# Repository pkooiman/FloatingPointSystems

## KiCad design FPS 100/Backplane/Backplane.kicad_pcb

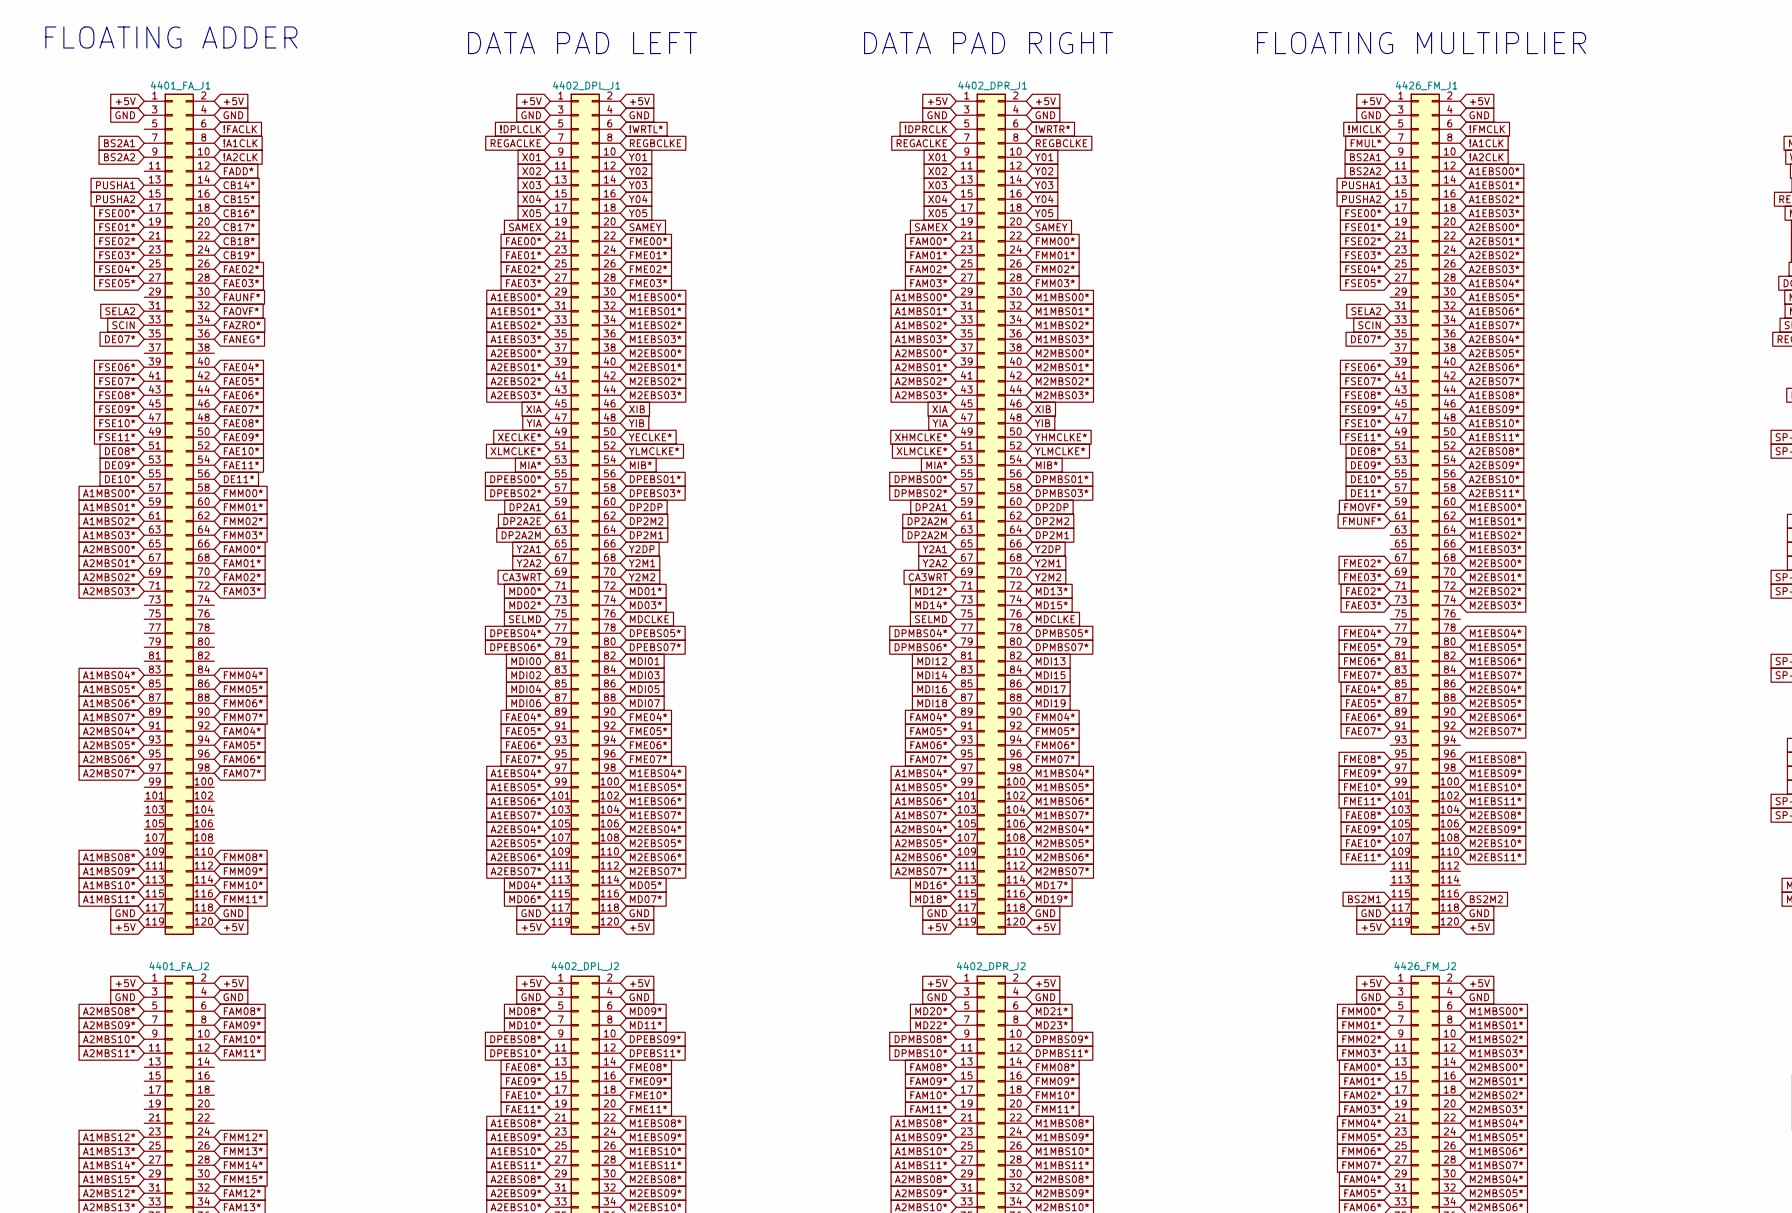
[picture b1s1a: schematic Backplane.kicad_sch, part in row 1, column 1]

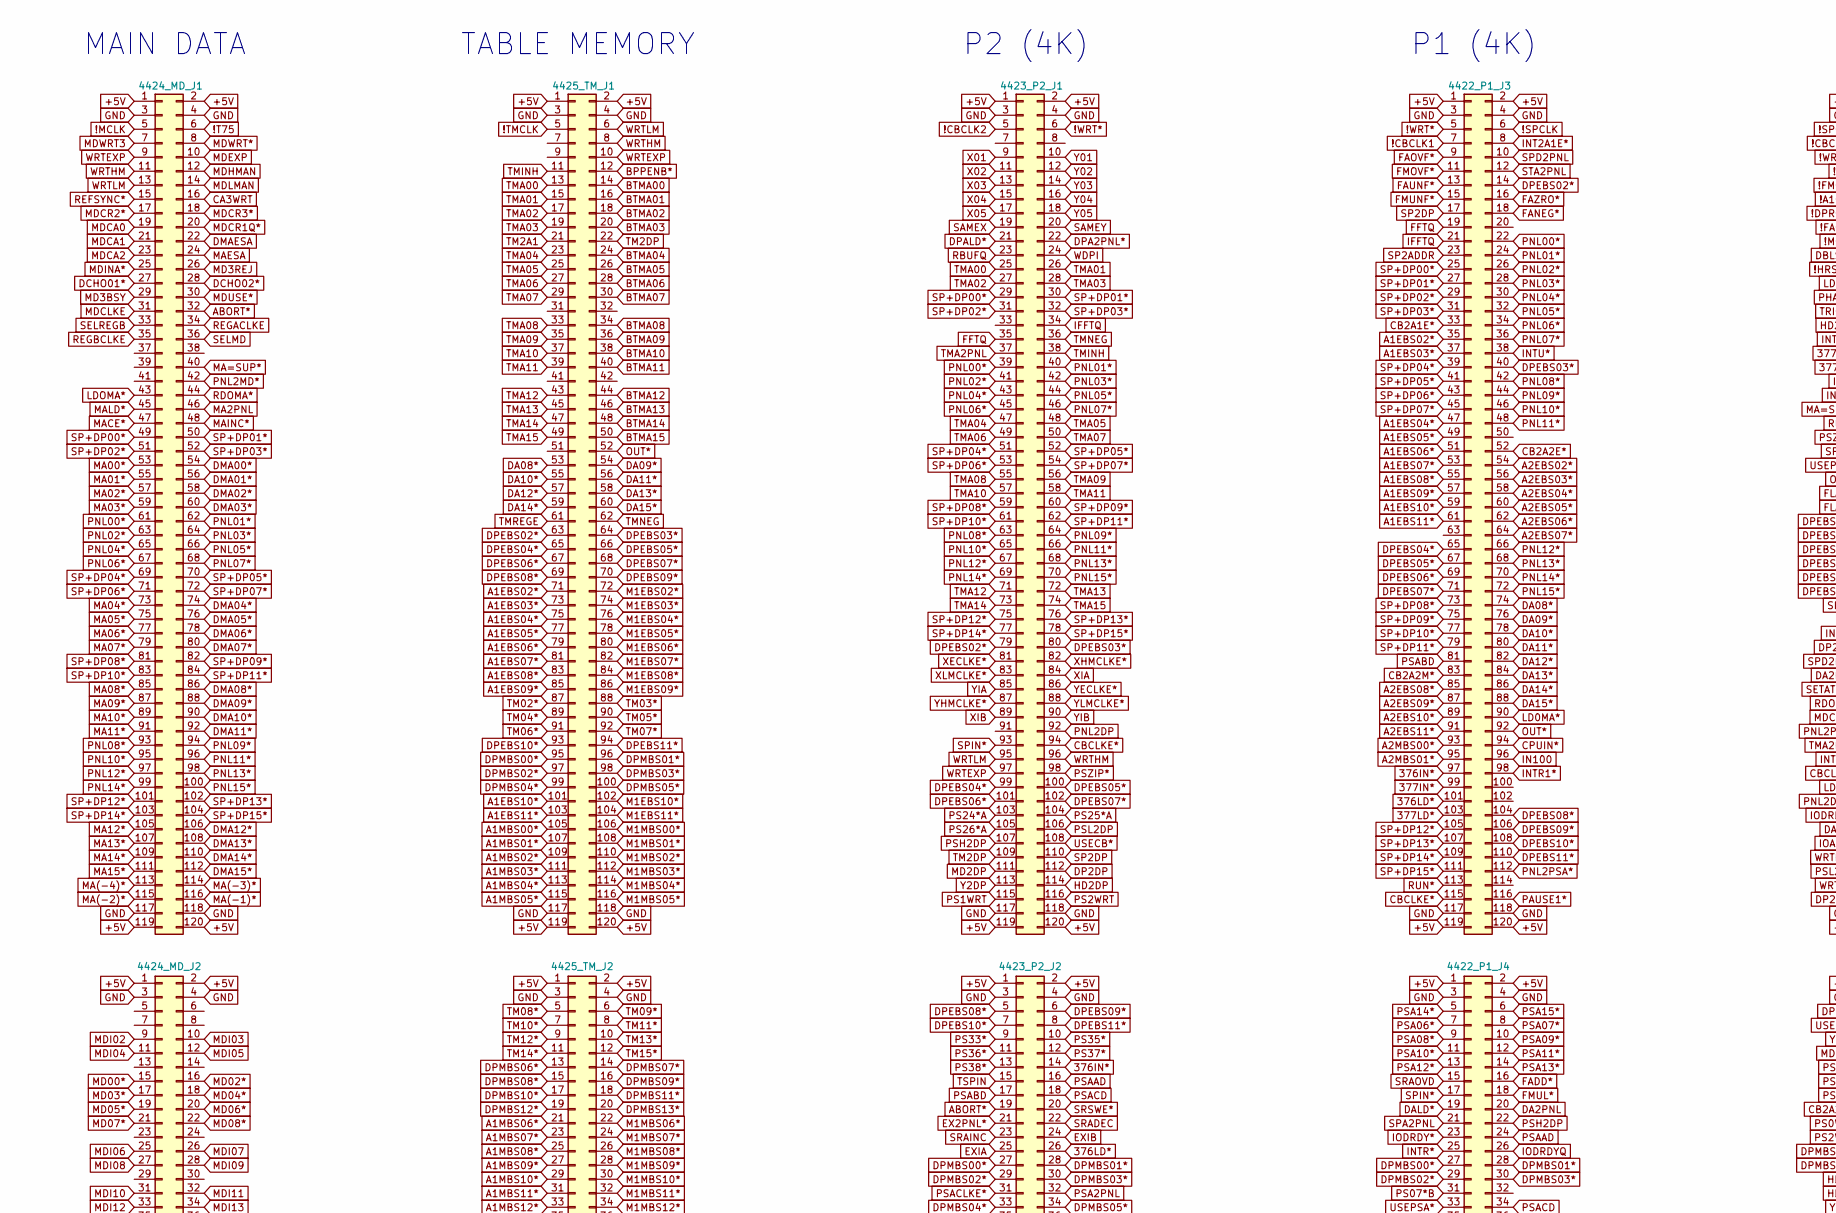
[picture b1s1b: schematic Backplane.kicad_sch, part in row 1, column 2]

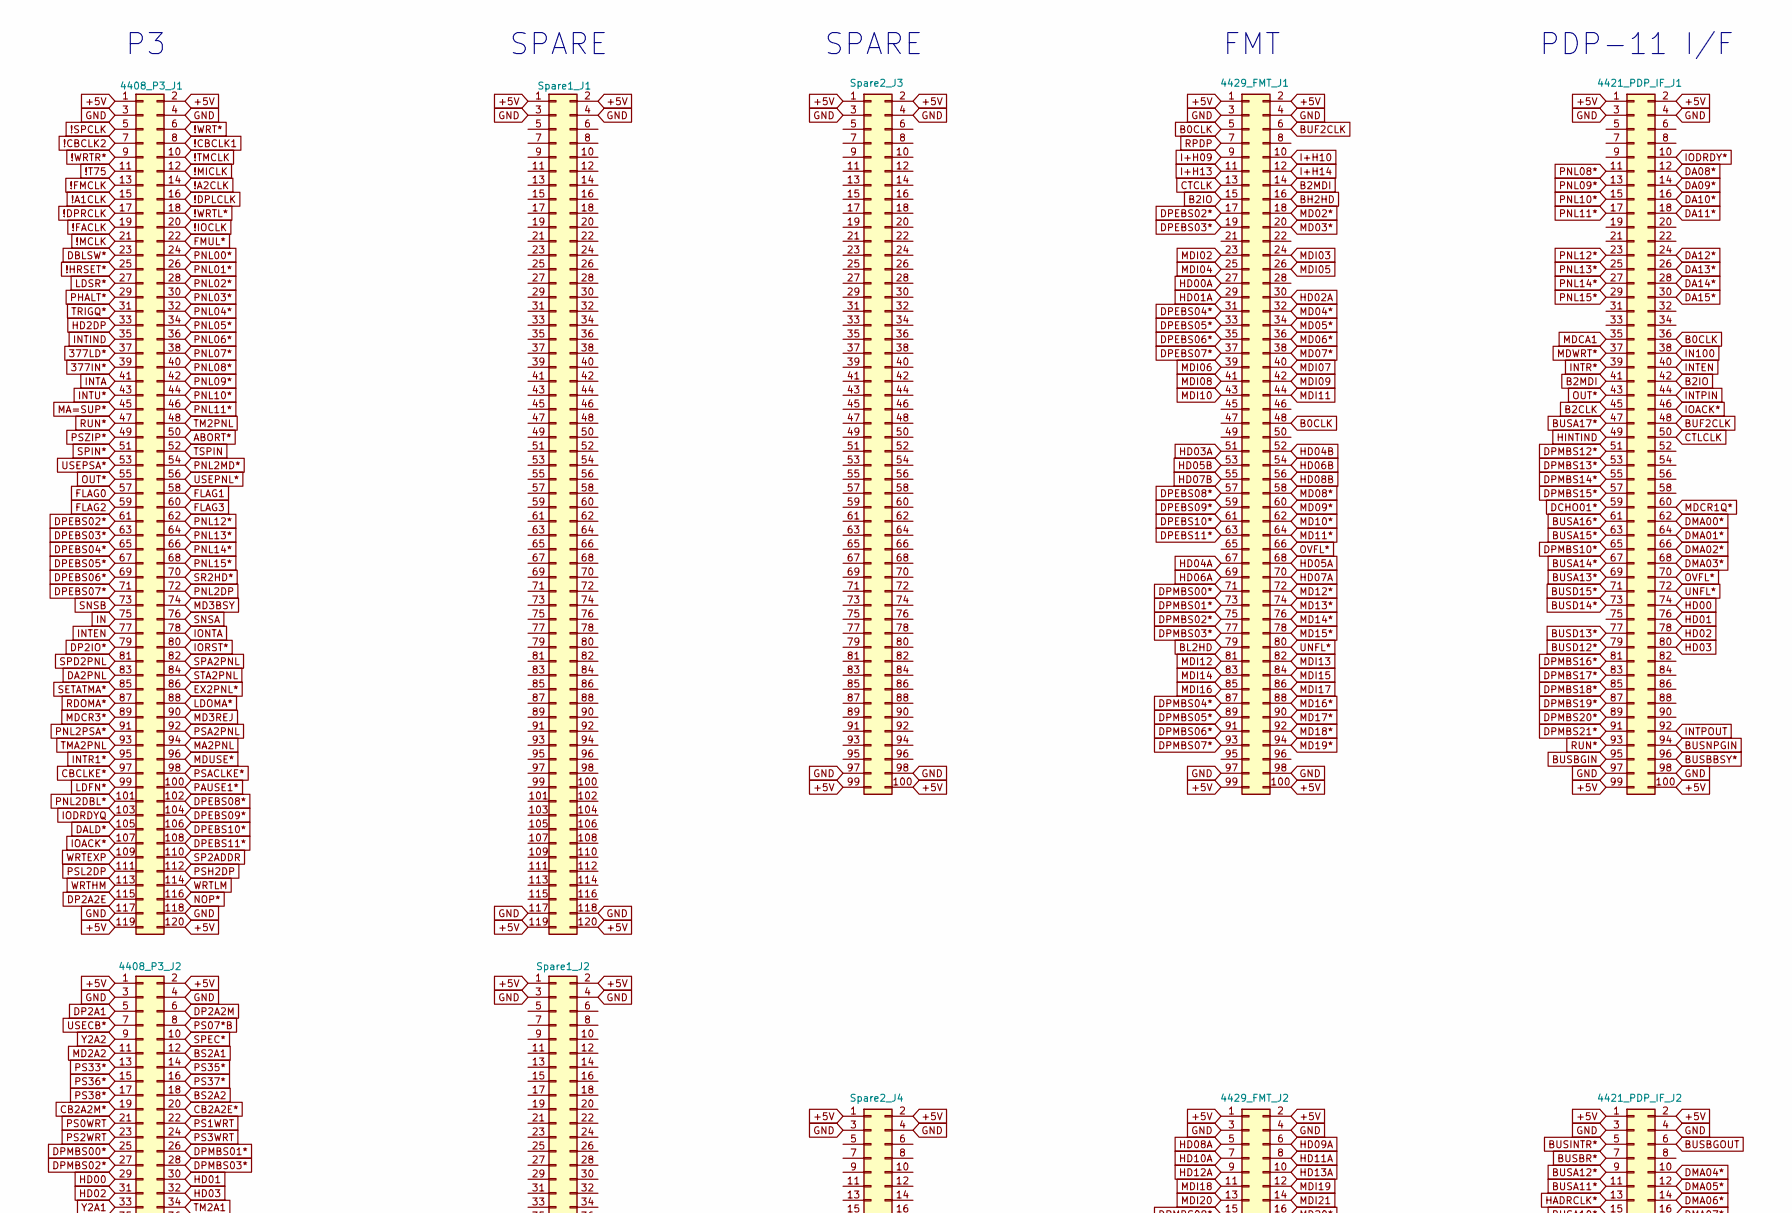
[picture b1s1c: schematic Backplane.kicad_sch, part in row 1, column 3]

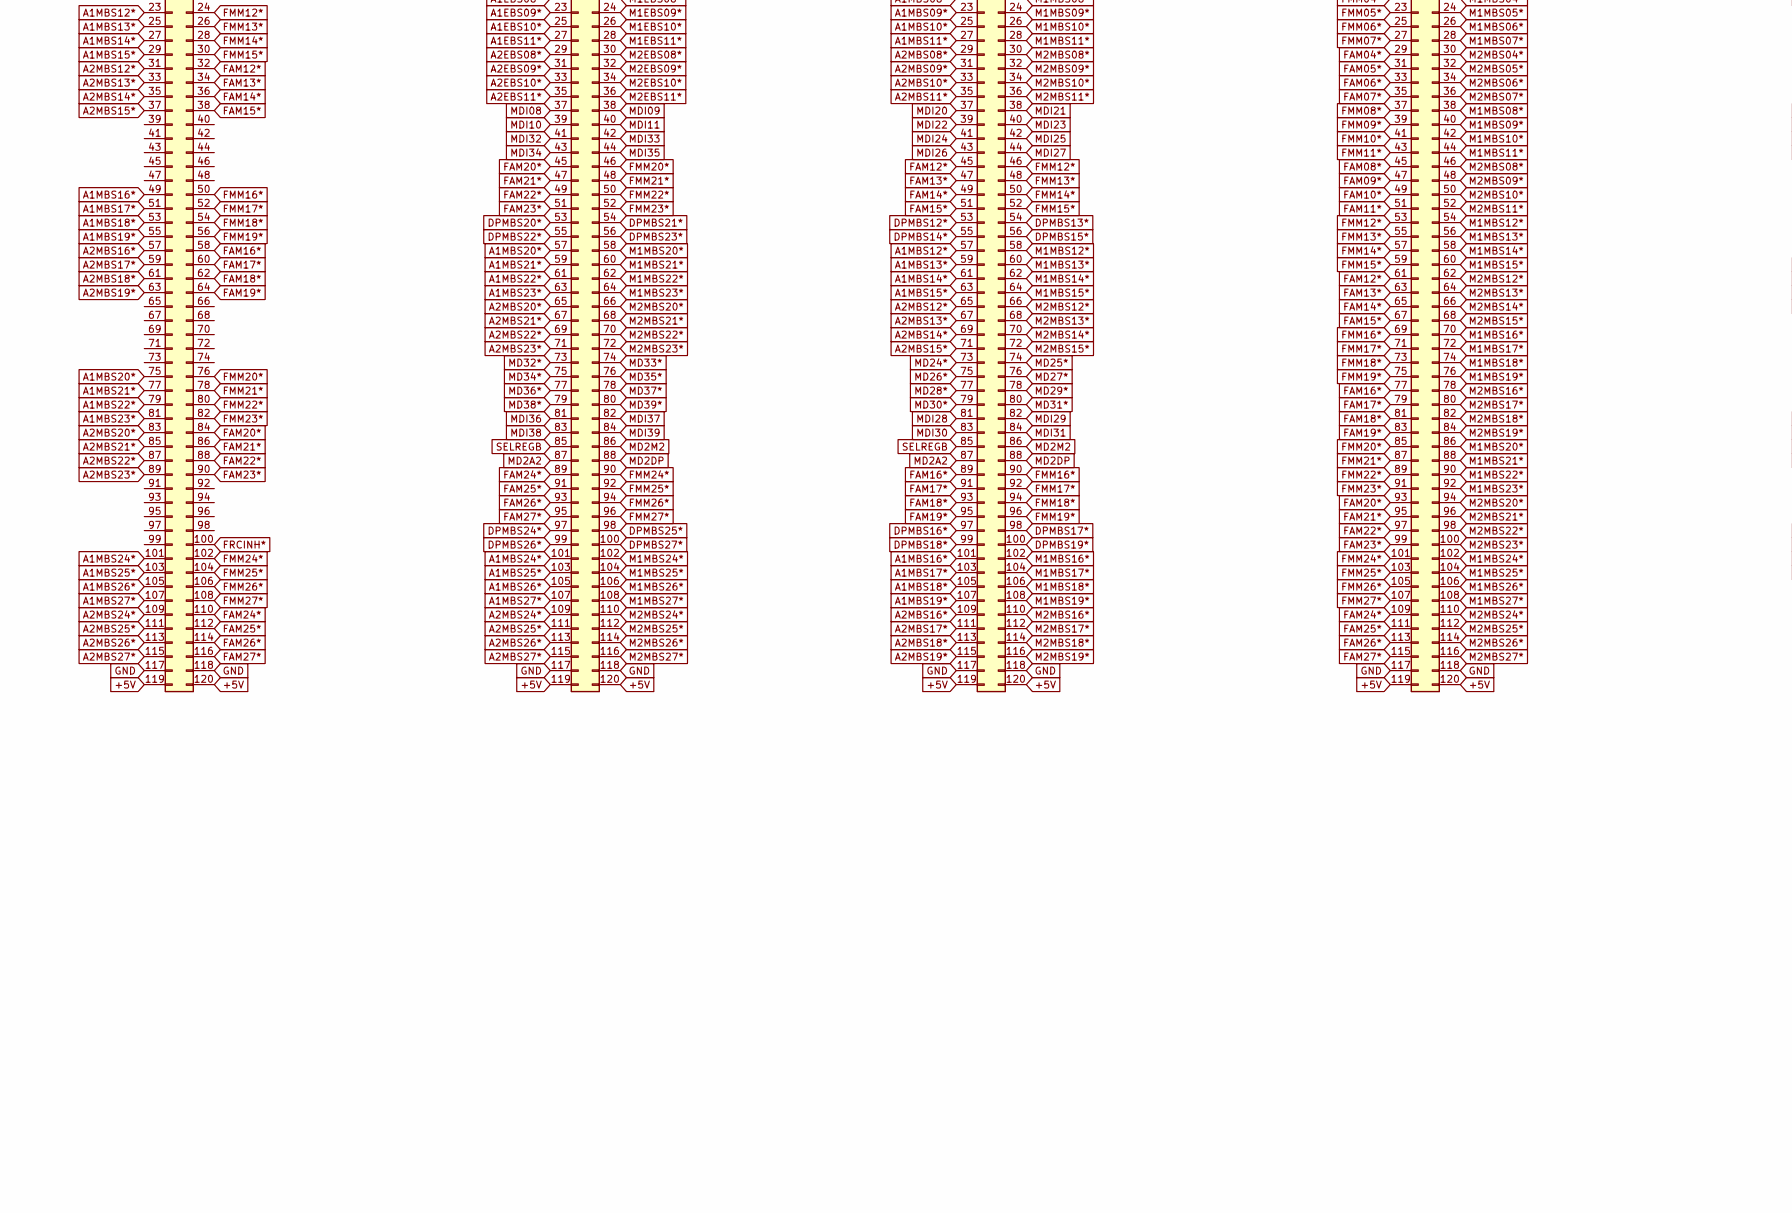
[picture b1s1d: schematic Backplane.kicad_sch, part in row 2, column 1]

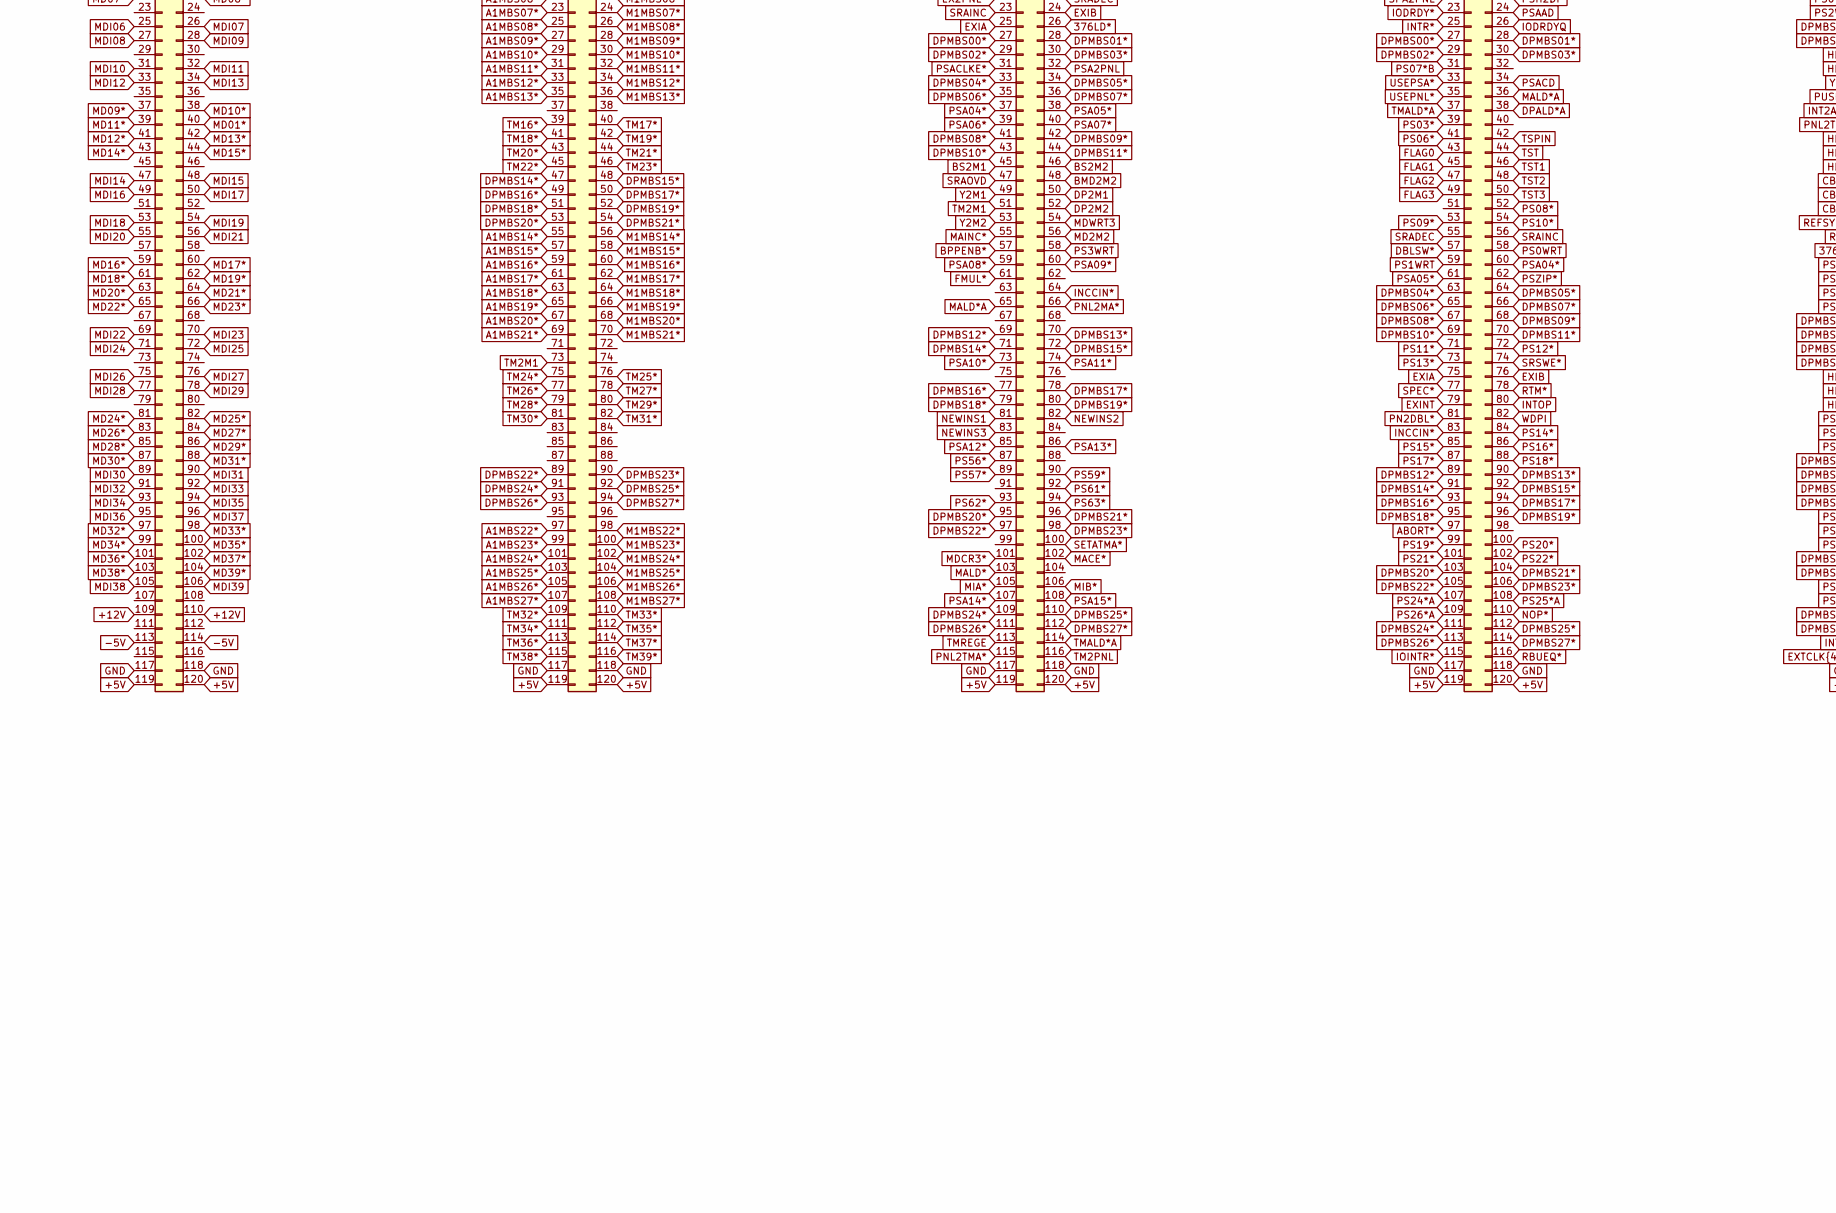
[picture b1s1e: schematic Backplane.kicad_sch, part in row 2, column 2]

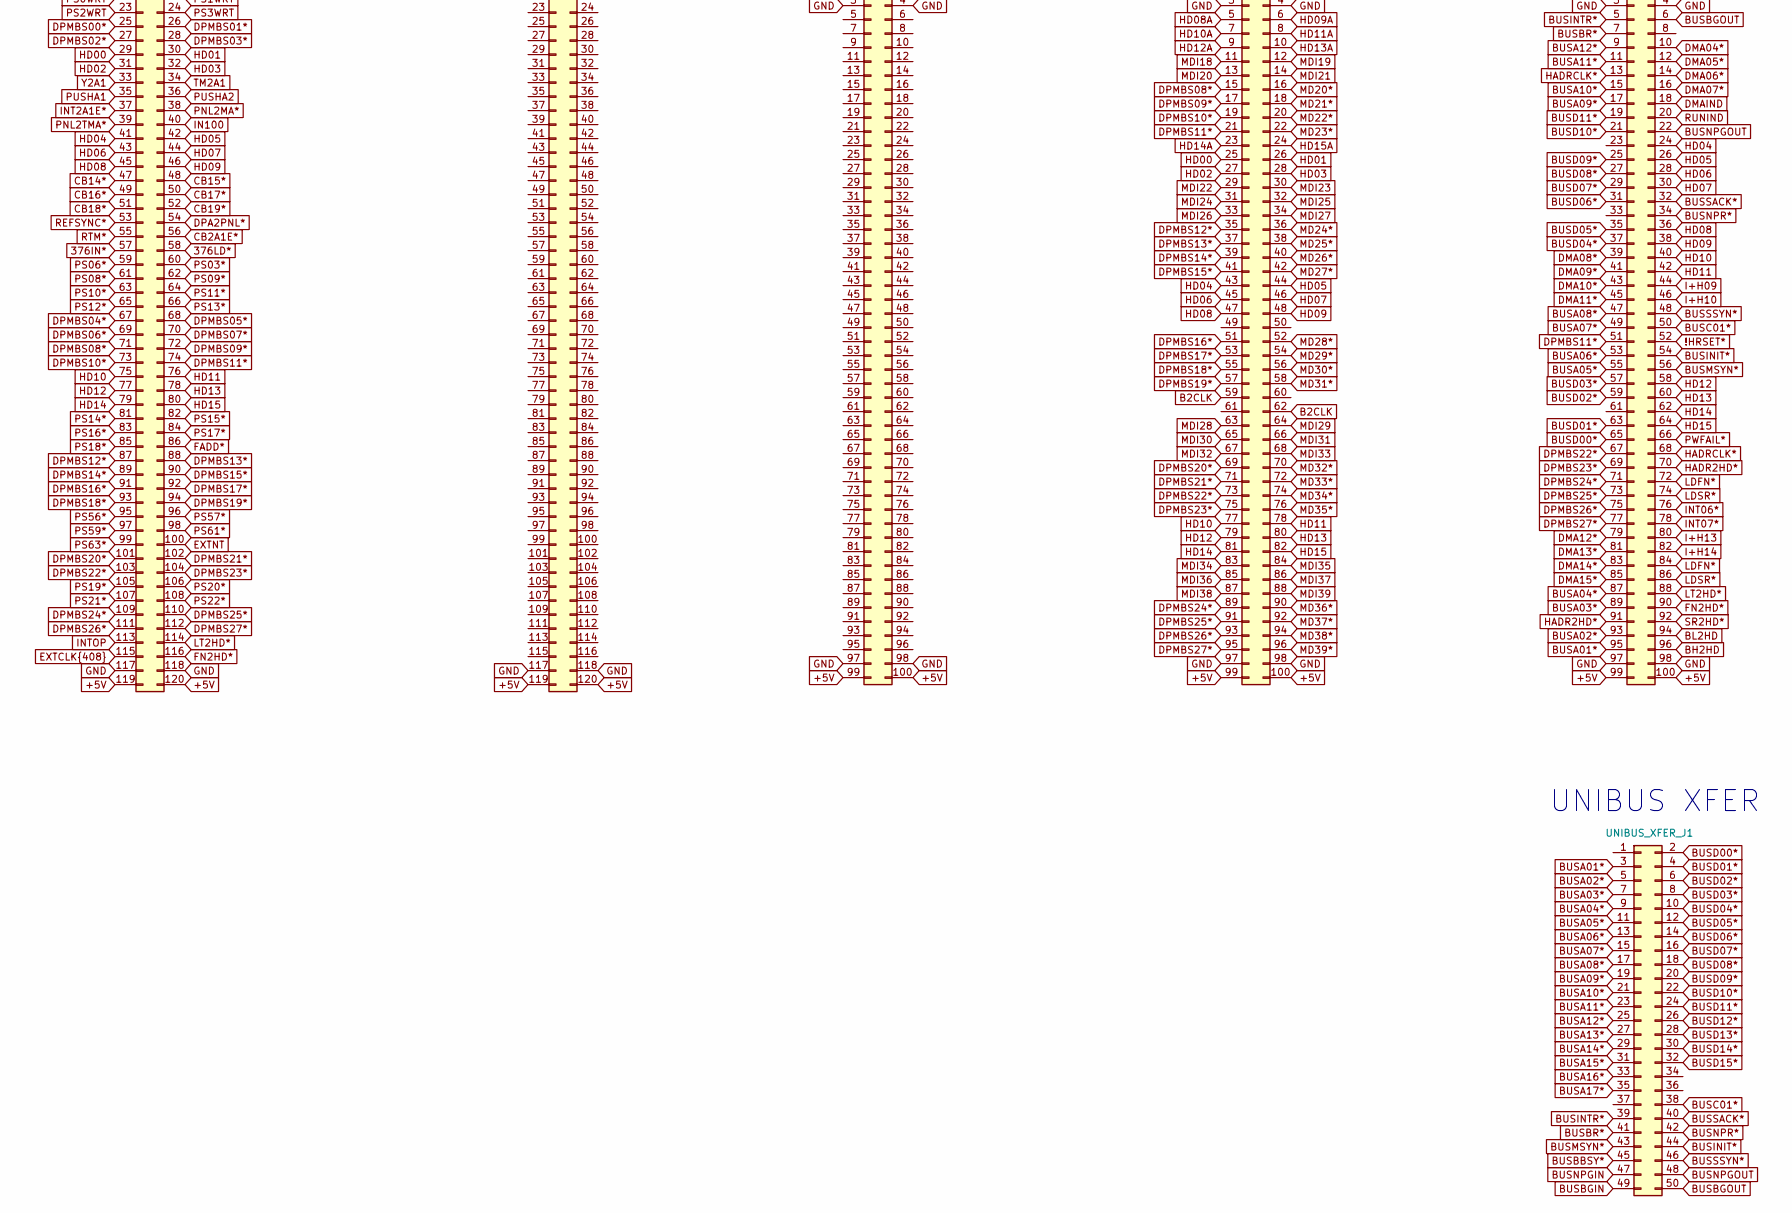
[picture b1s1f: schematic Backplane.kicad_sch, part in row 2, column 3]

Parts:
4401_FA_J1, 4401_FA_J2, 4402_DPL_J1, 4402_DPL_J2, 4402_DPR_J1, 4402_DPR_J2, 4408_P3_J1, 4408_P3_J2, 4422_P1_J3, 4422_P1_J4, 4423_P2_J1, 4423_P2_J2, 4424_MD_J1, 4424_MD_J2, 4425_TM_J1, 4425_TM_J2, 4426_FM_J1, 4426_FM_J2: Conn_02x60_120pin; 120pin_Edge_Connector
4421_PDP_IF_J1, 4421_PDP_IF_J2, 4429_FMT_J1, 4429_FMT_J2: Conn_02x50_100pin; 100pin_Edge_Connector
Spare1_J1, Spare1_J2: Conn_02x60_120pin; 120pin_Edge_Connector
Spare2_J3, Spare2_J4: Conn_02x50_100pin; 100pin_Edge_Connector
UNIBUS_XFER_J1: Conn_02x25_Odd_Even; PinHeader_2x25_P2.54mm_Vertical

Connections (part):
376IN*: 4408_P3_J2.57, 4422_P1_J3.97, 4423_P2_J2.14
376LD*: 4408_P3_J2.58, 4422_P1_J3.101, 4423_P2_J2.26
377IN*: 4408_P3_J1.39, 4422_P1_J3.99
377LD*: 4408_P3_J1.37, 4422_P1_J3.103
!A1CLK: 4401_FA_J1.8, 4408_P3_J1.15, 4426_FM_J1.8
!A2CLK: 4401_FA_J1.10, 4408_P3_J1.14, 4426_FM_J1.10
!CBCLK1: 4408_P3_J1.8, 4422_P1_J3.7
!CBCLK2: 4408_P3_J1.7, 4423_P2_J1.5
!DPLCLK: 4402_DPL_J1.5, 4408_P3_J1.16
!DPRCLK: 4402_DPR_J1.5, 4408_P3_J1.17
!FACLK: 4401_FA_J1.6, 4408_P3_J1.19
!FMCLK: 4408_P3_J1.13, 4426_FM_J1.6
!HRSET*: 4408_P3_J1.25, 4421_PDP_IF_J2.52
!IOCLK: 4408_P3_J1.20
!MCLK: 4408_P3_J1.21, 4424_MD_J1.5
!MICLK: 4408_P3_J1.12, 4426_FM_J1.5
!SPCLK: 4408_P3_J1.5, 4422_P1_J3.6
!T75: 4408_P3_J1.11, 4424_MD_J1.6
!TMCLK: 4408_P3_J1.10, 4425_TM_J1.5
!WRT*: 4408_P3_J1.6, 4422_P1_J3.5, 4423_P2_J1.6
!WRTL*: 4402_DPL_J1.6, 4408_P3_J1.18
!WRTR*: 4402_DPR_J1.6, 4408_P3_J1.9
+5V: 4401_FA_J1.1, 4401_FA_J1.2, 4401_FA_J1.119, 4401_FA_J1.120, 4401_FA_J2.1, 4401_FA_J2.2, 4401_FA_J2.119, 4401_FA_J2.120, 4402_DPL_J1.1, 4402_DPL_J1.2, 4402_DPL_J1.119, 4402_DPL_J1.120, 4402_DPL_J2.1, 4402_DPL_J2.2, 4402_DPL_J2.119, 4402_DPL_J2.120, 4402_DPR_J1.1, 4402_DPR_J1.2, 4402_DPR_J1.119, 4402_DPR_J1.120, 4402_DPR_J2.1, 4402_DPR_J2.2, 4402_DPR_J2.119, 4402_DPR_J2.120, 4408_P3_J1.1, 4408_P3_J1.2, 4408_P3_J1.119, 4408_P3_J1.120, 4408_P3_J2.1, 4408_P3_J2.2, 4408_P3_J2.119, 4408_P3_J2.120, 4421_PDP_IF_J1.1, 4421_PDP_IF_J1.2, 4421_PDP_IF_J1.99, 4421_PDP_IF_J1.100, 4421_PDP_IF_J2.1, 4421_PDP_IF_J2.2, 4421_PDP_IF_J2.99, 4421_PDP_IF_J2.100, 4422_P1_J3.1, 4422_P1_J3.2, 4422_P1_J3.119, 4422_P1_J3.120, 4422_P1_J4.1, 4422_P1_J4.2, 4422_P1_J4.119, 4422_P1_J4.120, 4423_P2_J1.1, 4423_P2_J1.2, 4423_P2_J1.119, 4423_P2_J1.120, 4423_P2_J2.1, 4423_P2_J2.2, 4423_P2_J2.119, 4423_P2_J2.120, 4424_MD_J1.1, 4424_MD_J1.2, 4424_MD_J1.119, 4424_MD_J1.120, 4424_MD_J2.1, 4424_MD_J2.2, 4424_MD_J2.119, 4424_MD_J2.120, 4425_TM_J1.1, 4425_TM_J1.2, 4425_TM_J1.119, 4425_TM_J1.120, 4425_TM_J2.1, 4425_TM_J2.2, 4425_TM_J2.119, 4425_TM_J2.120, 4426_FM_J1.1, 4426_FM_J1.2, 4426_FM_J1.119, 4426_FM_J1.120, 4426_FM_J2.1, 4426_FM_J2.2, 4426_FM_J2.119, 4426_FM_J2.120, 4429_FMT_J1.1, 4429_FMT_J1.2, 4429_FMT_J1.99, 4429_FMT_J1.100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
+12V: 4424_MD_J2.109, 4424_MD_J2.110
-5V: 4424_MD_J2.113, 4424_MD_J2.114
A1EBS00*: 4402_DPL_J1.29, 4426_FM_J1.12
A1EBS01*: 4402_DPL_J1.31, 4426_FM_J1.14
A1EBS02*: 4402_DPL_J1.33, 4422_P1_J3.35, 4425_TM_J1.71, 4426_FM_J1.16
A1EBS03*: 4402_DPL_J1.35, 4422_P1_J3.37, 4425_TM_J1.73, 4426_FM_J1.18
A1EBS04*: 4402_DPL_J1.97, 4422_P1_J3.47, 4425_TM_J1.75, 4426_FM_J1.28
A1EBS05*: 4402_DPL_J1.99, 4422_P1_J3.49, 4425_TM_J1.77, 4426_FM_J1.30
A1EBS06*: 4402_DPL_J1.101, 4422_P1_J3.51, 4425_TM_J1.79, 4426_FM_J1.32
A1EBS07*: 4402_DPL_J1.103, 4422_P1_J3.53, 4425_TM_J1.81, 4426_FM_J1.34
A1EBS08*: 4402_DPL_J2.21, 4422_P1_J3.55, 4425_TM_J1.83, 4426_FM_J1.44
A1EBS09*: 4402_DPL_J2.23, 4422_P1_J3.57, 4425_TM_J1.85, 4426_FM_J1.46
A1EBS10*: 4402_DPL_J2.25, 4422_P1_J3.59, 4425_TM_J1.101, 4426_FM_J1.48
A1EBS11*: 4402_DPL_J2.27, 4422_P1_J3.61, 4425_TM_J1.103, 4426_FM_J1.50
A1MBS00*: 4401_FA_J1.57, 4402_DPR_J1.29, 4425_TM_J1.105
A1MBS01*: 4401_FA_J1.59, 4402_DPR_J1.31, 4425_TM_J1.107
A1MBS02*: 4401_FA_J1.61, 4402_DPR_J1.33, 4425_TM_J1.109
A1MBS03*: 4401_FA_J1.63, 4402_DPR_J1.35, 4425_TM_J1.111
A1MBS04*: 4401_FA_J1.83, 4402_DPR_J1.97, 4425_TM_J1.113
A1MBS05*: 4401_FA_J1.85, 4402_DPR_J1.99, 4425_TM_J1.115
A1MBS06*: 4401_FA_J1.87, 4402_DPR_J1.101, 4425_TM_J2.21
A1MBS07*: 4401_FA_J1.89, 4402_DPR_J1.103, 4425_TM_J2.23
A1MBS08*: 4401_FA_J1.109, 4402_DPR_J2.21, 4425_TM_J2.25
A1MBS09*: 4401_FA_J1.111, 4402_DPR_J2.23, 4425_TM_J2.27
A1MBS10*: 4401_FA_J1.113, 4402_DPR_J2.25, 4425_TM_J2.29
A1MBS11*: 4401_FA_J1.115, 4402_DPR_J2.27, 4425_TM_J2.31
A1MBS12*: 4401_FA_J2.23, 4402_DPR_J2.57, 4425_TM_J2.33
A1MBS13*: 4401_FA_J2.25, 4402_DPR_J2.59, 4425_TM_J2.35
A1MBS14*: 4401_FA_J2.27, 4402_DPR_J2.61, 4425_TM_J2.55
A1MBS15*: 4401_FA_J2.29, 4402_DPR_J2.63, 4425_TM_J2.57
A1MBS16*: 4401_FA_J2.49, 4402_DPR_J2.101, 4425_TM_J2.59
A1MBS17*: 4401_FA_J2.51, 4402_DPR_J2.103, 4425_TM_J2.61
A1MBS18*: 4401_FA_J2.53, 4402_DPR_J2.105, 4425_TM_J2.63
A1MBS19*: 4401_FA_J2.55, 4402_DPR_J2.107, 4425_TM_J2.65
A1MBS20*: 4401_FA_J2.75, 4402_DPL_J2.57, 4425_TM_J2.67
A1MBS21*: 4401_FA_J2.77, 4402_DPL_J2.59, 4425_TM_J2.69
A1MBS22*: 4401_FA_J2.79, 4402_DPL_J2.61, 4425_TM_J2.97
A1MBS23*: 4401_FA_J2.81, 4402_DPL_J2.63, 4425_TM_J2.99
A1MBS24*: 4401_FA_J2.101, 4402_DPL_J2.101, 4425_TM_J2.101
A1MBS25*: 4401_FA_J2.103, 4402_DPL_J2.103, 4425_TM_J2.103
A1MBS26*: 4401_FA_J2.105, 4402_DPL_J2.105, 4425_TM_J2.105
A1MBS27*: 4401_FA_J2.107, 4402_DPL_J2.107, 4425_TM_J2.107
A2EBS00*: 4402_DPL_J1.37, 4426_FM_J1.20
A2EBS01*: 4402_DPL_J1.39, 4426_FM_J1.22
A2EBS02*: 4402_DPL_J1.41, 4422_P1_J3.54, 4426_FM_J1.24
A2EBS03*: 4402_DPL_J1.43, 4422_P1_J3.56, 4426_FM_J1.26
A2EBS04*: 4402_DPL_J1.105, 4422_P1_J3.58, 4426_FM_J1.36
A2EBS05*: 4402_DPL_J1.107, 4422_P1_J3.60, 4426_FM_J1.38
A2EBS06*: 4402_DPL_J1.109, 4422_P1_J3.62, 4426_FM_J1.40
A2EBS07*: 4402_DPL_J1.111, 4422_P1_J3.64, 4426_FM_J1.42
A2EBS08*: 4402_DPL_J2.29, 4422_P1_J3.85, 4426_FM_J1.52
A2EBS09*: 4402_DPL_J2.31, 4422_P1_J3.87, 4426_FM_J1.54
A2EBS10*: 4402_DPL_J2.33, 4422_P1_J3.89, 4426_FM_J1.56
A2EBS11*: 4402_DPL_J2.35, 4422_P1_J3.91, 4426_FM_J1.58
A2MBS00*: 4401_FA_J1.65, 4402_DPR_J1.37, 4422_P1_J3.93
A2MBS01*: 4401_FA_J1.67, 4402_DPR_J1.39, 4422_P1_J3.95
A2MBS02*: 4401_FA_J1.69, 4402_DPR_J1.41
A2MBS03*: 4401_FA_J1.71, 4402_DPR_J1.43
A2MBS04*: 4401_FA_J1.91, 4402_DPR_J1.105
A2MBS05*: 4401_FA_J1.93, 4402_DPR_J1.107
A2MBS06*: 4401_FA_J1.95, 4402_DPR_J1.109
A2MBS07*: 4401_FA_J1.97, 4402_DPR_J1.111
A2MBS08*: 4401_FA_J2.5, 4402_DPR_J2.29
A2MBS09*: 4401_FA_J2.7, 4402_DPR_J2.31
A2MBS10*: 4401_FA_J2.9, 4402_DPR_J2.33
A2MBS11*: 4401_FA_J2.11, 4402_DPR_J2.35
A2MBS12*: 4401_FA_J2.31, 4402_DPR_J2.65
A2MBS13*: 4401_FA_J2.33, 4402_DPR_J2.67
A2MBS14*: 4401_FA_J2.35, 4402_DPR_J2.69
A2MBS15*: 4401_FA_J2.37, 4402_DPR_J2.71
A2MBS16*: 4401_FA_J2.57, 4402_DPR_J2.109
A2MBS17*: 4401_FA_J2.59, 4402_DPR_J2.111
A2MBS18*: 4401_FA_J2.61, 4402_DPR_J2.113
A2MBS19*: 4401_FA_J2.63, 4402_DPR_J2.115
A2MBS20*: 4401_FA_J2.83, 4402_DPL_J2.65
A2MBS21*: 4401_FA_J2.85, 4402_DPL_J2.67
A2MBS22*: 4401_FA_J2.87, 4402_DPL_J2.69
A2MBS23*: 4401_FA_J2.89, 4402_DPL_J2.71
A2MBS24*: 4401_FA_J2.109, 4402_DPL_J2.109
A2MBS25*: 4401_FA_J2.111, 4402_DPL_J2.111
A2MBS26*: 4401_FA_J2.113, 4402_DPL_J2.113
A2MBS27*: 4401_FA_J2.115, 4402_DPL_J2.115
ABORT*: 4408_P3_J1.50, 4422_P1_J4.97, 4423_P2_J2.19, 4424_MD_J1.32
B0CLK: 4421_PDP_IF_J1.36, 4429_FMT_J1.5, 4429_FMT_J1.48
B2CLK: 4421_PDP_IF_J1.45, 4429_FMT_J2.59, 4429_FMT_J2.62
B2IO: 4421_PDP_IF_J1.42, 4429_FMT_J1.15
B2MDI: 4421_PDP_IF_J1.41, 4429_FMT_J1.14
BH2HD: 4421_PDP_IF_J2.96, 4429_FMT_J1.16
BL2HD: 4421_PDP_IF_J2.94, 4429_FMT_J1.79
BMD2M2: 4423_P2_J2.48
BPPENB*: 4423_P2_J2.57, 4425_TM_J1.12
BS2A1: 4401_FA_J1.7, 4408_P3_J2.12, 4426_FM_J1.9
BS2A2: 4401_FA_J1.9, 4408_P3_J2.18, 4426_FM_J1.11
BS2M1: 4423_P2_J2.45, 4426_FM_J1.115
BS2M2: 4423_P2_J2.46, 4426_FM_J1.116
BTMA00: 4425_TM_J1.14
BTMA01: 4425_TM_J1.16
BTMA02: 4425_TM_J1.18
BTMA03: 4425_TM_J1.20
BTMA04: 4425_TM_J1.24
BTMA05: 4425_TM_J1.26
BTMA06: 4425_TM_J1.28
BTMA07: 4425_TM_J1.30
BTMA08: 4425_TM_J1.34
BTMA09: 4425_TM_J1.36
BTMA10: 4425_TM_J1.38
BTMA11: 4425_TM_J1.40
BTMA12: 4425_TM_J1.44
BTMA13: 4425_TM_J1.46
BTMA14: 4425_TM_J1.48
BTMA15: 4425_TM_J1.50
BUF2CLK: 4421_PDP_IF_J1.48, 4429_FMT_J1.6
BUSA01*: 4421_PDP_IF_J2.95, UNIBUS_XFER_J1.3
BUSA02*: 4421_PDP_IF_J2.93, UNIBUS_XFER_J1.5
BUSA03*: 4421_PDP_IF_J2.89, UNIBUS_XFER_J1.7
BUSA04*: 4421_PDP_IF_J2.87, UNIBUS_XFER_J1.9
BUSA05*: 4421_PDP_IF_J2.55, UNIBUS_XFER_J1.11
BUSA06*: 4421_PDP_IF_J2.53, UNIBUS_XFER_J1.13
BUSA07*: 4421_PDP_IF_J2.49, UNIBUS_XFER_J1.15
BUSA08*: 4421_PDP_IF_J2.47, UNIBUS_XFER_J1.17
BUSA09*: 4421_PDP_IF_J2.17, UNIBUS_XFER_J1.19
BUSA10*: 4421_PDP_IF_J2.15, UNIBUS_XFER_J1.21
BUSA11*: 4421_PDP_IF_J2.11, UNIBUS_XFER_J1.23
BUSA12*: 4421_PDP_IF_J2.9, UNIBUS_XFER_J1.25
BUSA13*: 4421_PDP_IF_J1.69, UNIBUS_XFER_J1.27
BUSA14*: 4421_PDP_IF_J1.67, UNIBUS_XFER_J1.29
BUSA15*: 4421_PDP_IF_J1.63, UNIBUS_XFER_J1.31
BUSA16*: 4421_PDP_IF_J1.61, UNIBUS_XFER_J1.33
BUSA17*: 4421_PDP_IF_J1.47, UNIBUS_XFER_J1.35
BUSBBSY*: 4421_PDP_IF_J1.96, UNIBUS_XFER_J1.45
BUSBGIN: 4421_PDP_IF_J1.95, UNIBUS_XFER_J1.49
BUSBGOUT: 4421_PDP_IF_J2.6, UNIBUS_XFER_J1.50
BUSBR*: 4421_PDP_IF_J2.7, UNIBUS_XFER_J1.41
BUSC01*: 4421_PDP_IF_J2.50, UNIBUS_XFER_J1.38
BUSD00*: 4421_PDP_IF_J2.65, UNIBUS_XFER_J1.2
BUSD01*: 4421_PDP_IF_J2.63, UNIBUS_XFER_J1.4
BUSD02*: 4421_PDP_IF_J2.59, UNIBUS_XFER_J1.6
BUSD03*: 4421_PDP_IF_J2.57, UNIBUS_XFER_J1.8
BUSD04*: 4421_PDP_IF_J2.37, UNIBUS_XFER_J1.10
BUSD05*: 4421_PDP_IF_J2.35, UNIBUS_XFER_J1.12
BUSD06*: 4421_PDP_IF_J2.31, UNIBUS_XFER_J1.14
BUSD07*: 4421_PDP_IF_J2.29, UNIBUS_XFER_J1.16
BUSD08*: 4421_PDP_IF_J2.27, UNIBUS_XFER_J1.18
BUSD09*: 4421_PDP_IF_J2.25, UNIBUS_XFER_J1.20
BUSD10*: 4421_PDP_IF_J2.21, UNIBUS_XFER_J1.22
BUSD11*: 4421_PDP_IF_J2.19, UNIBUS_XFER_J1.24
BUSD12*: 4421_PDP_IF_J1.79, UNIBUS_XFER_J1.26
BUSD13*: 4421_PDP_IF_J1.77, UNIBUS_XFER_J1.28
BUSD14*: 4421_PDP_IF_J1.73, UNIBUS_XFER_J1.30
BUSD15*: 4421_PDP_IF_J1.71, UNIBUS_XFER_J1.32
BUSINIT*: 4421_PDP_IF_J2.54, UNIBUS_XFER_J1.44
BUSINTR*: 4421_PDP_IF_J2.5, UNIBUS_XFER_J1.39
BUSMSYN*: 4421_PDP_IF_J2.56, UNIBUS_XFER_J1.43
BUSNPGIN: 4421_PDP_IF_J1.94, UNIBUS_XFER_J1.47
BUSNPGOUT: 4421_PDP_IF_J2.22, UNIBUS_XFER_J1.48
BUSNPR*: 4421_PDP_IF_J2.34, UNIBUS_XFER_J1.42
BUSSACK*: 4421_PDP_IF_J2.32, UNIBUS_XFER_J1.40
BUSSSYN*: 4421_PDP_IF_J2.48, UNIBUS_XFER_J1.46
CA3WRT: 4402_DPL_J1.69, 4402_DPR_J1.69, 4424_MD_J1.16
CB2A1E*: 4408_P3_J2.56, 4422_P1_J3.33
CB2A2E*: 4408_P3_J2.20, 4422_P1_J3.52
CB2A2M*: 4408_P3_J2.19, 4422_P1_J3.83
CB14*: 4401_FA_J1.14, 4408_P3_J2.47
CB15*: 4401_FA_J1.16, 4408_P3_J2.48
CB16*: 4401_FA_J1.18, 4408_P3_J2.49
CB17*: 4401_FA_J1.20, 4408_P3_J2.50
CB18*: 4401_FA_J1.22, 4408_P3_J2.51
CB19*: 4401_FA_J1.24, 4408_P3_J2.52
CBCLKE*: 4408_P3_J1.97, 4422_P1_J3.115, 4423_P2_J1.94
CPUIN*: 4422_P1_J3.94
CTCLK: 4429_FMT_J1.13
CTLCLK: 4421_PDP_IF_J1.50
DA2PNL: 4408_P3_J1.83, 4422_P1_J4.20
DA08*: 4421_PDP_IF_J1.12, 4422_P1_J3.74, 4425_TM_J1.53
DA09*: 4421_PDP_IF_J1.14, 4422_P1_J3.76, 4425_TM_J1.54
DA10*: 4421_PDP_IF_J1.16, 4422_P1_J3.78, 4425_TM_J1.55
DA11*: 4421_PDP_IF_J1.18, 4422_P1_J3.80, 4425_TM_J1.56
DA12*: 4421_PDP_IF_J1.24, 4422_P1_J3.82, 4425_TM_J1.57
DA13*: 4421_PDP_IF_J1.26, 4422_P1_J3.84, 4425_TM_J1.58
DA14*: 4421_PDP_IF_J1.28, 4422_P1_J3.86, 4425_TM_J1.59
DA15*: 4421_PDP_IF_J1.30, 4422_P1_J3.88, 4425_TM_J1.60
DALD*: 4408_P3_J1.105, 4422_P1_J4.19
DBLSW*: 4408_P3_J1.23, 4422_P1_J4.57
DCHO01*: 4421_PDP_IF_J1.59, 4424_MD_J1.27
DCHO02*: 4424_MD_J1.28
DE07*: 4401_FA_J1.35, 4426_FM_J1.35
DE08*: 4401_FA_J1.51, 4426_FM_J1.51
DE09*: 4401_FA_J1.53, 4426_FM_J1.53
DE10*: 4401_FA_J1.55, 4426_FM_J1.55
DE11*: 4401_FA_J1.56, 4426_FM_J1.57
DMA00*: 4421_PDP_IF_J1.62, 4424_MD_J1.54
DMA01*: 4421_PDP_IF_J1.64, 4424_MD_J1.56
DMA02*: 4421_PDP_IF_J1.66, 4424_MD_J1.58
DMA03*: 4421_PDP_IF_J1.68, 4424_MD_J1.60
DMA04*: 4421_PDP_IF_J2.10, 4424_MD_J1.74
DMA05*: 4421_PDP_IF_J2.12, 4424_MD_J1.76
DMA06*: 4421_PDP_IF_J2.14, 4424_MD_J1.78
DMA07*: 4421_PDP_IF_J2.16, 4424_MD_J1.80
DMA08*: 4421_PDP_IF_J2.39, 4424_MD_J1.86
DMA09*: 4421_PDP_IF_J2.41, 4424_MD_J1.88
DMA10*: 4421_PDP_IF_J2.43, 4424_MD_J1.90
DMA11*: 4421_PDP_IF_J2.45, 4424_MD_J1.92
DMA12*: 4421_PDP_IF_J2.79, 4424_MD_J1.106
DMA13*: 4421_PDP_IF_J2.81, 4424_MD_J1.108
DMA14*: 4421_PDP_IF_J2.83, 4424_MD_J1.110
DMA15*: 4421_PDP_IF_J2.85, 4424_MD_J1.112
DMAESA: 4424_MD_J1.22
DMAIND: 4421_PDP_IF_J2.18
DP2A1: 4402_DPL_J1.59, 4402_DPR_J1.59, 4408_P3_J2.5
DP2A2E: 4402_DPL_J1.61, 4408_P3_J1.115
DP2A2M: 4402_DPL_J1.63, 4402_DPR_J1.61, 4402_DPR_J1.63, 4408_P3_J2.6
DP2DP: 4402_DPL_J1.60, 4402_DPR_J1.60, 4423_P2_J1.112
DP2IO*: 4408_P3_J1.79
DP2M1: 4402_DPL_J1.64, 4402_DPR_J1.64, 4423_P2_J2.50
DP2M2: 4402_DPL_J1.62, 4402_DPR_J1.62, 4423_P2_J2.52
DPA2PNL*: 4408_P3_J2.54, 4423_P2_J1.22
DPALD*: 4423_P2_J1.21
DPALD*A: 4422_P1_J4.38
DPEBS00*: 4402_DPL_J1.55
DPEBS01*: 4402_DPL_J1.56
DPEBS02*: 4402_DPL_J1.57, 4408_P3_J1.61, 4422_P1_J3.14, 4423_P2_J1.79, 4425_TM_J1.63, 4429_FMT_J1.17
DPEBS03*: 4402_DPL_J1.58, 4408_P3_J1.63, 4422_P1_J3.40, 4423_P2_J1.80, 4425_TM_J1.64, 4429_FMT_J1.19
DPEBS04*: 4402_DPL_J1.77, 4408_P3_J1.65, 4422_P1_J3.65, 4423_P2_J1.99, 4425_TM_J1.65, 4429_FMT_J1.31
DPEBS05*: 4402_DPL_J1.78, 4408_P3_J1.67, 4422_P1_J3.67, 4423_P2_J1.100, 4425_TM_J1.66, 4429_FMT_J1.33
DPEBS06*: 4402_DPL_J1.79, 4408_P3_J1.69, 4422_P1_J3.69, 4423_P2_J1.101, 4425_TM_J1.67, 4429_FMT_J1.35
DPEBS07*: 4402_DPL_J1.80, 4408_P3_J1.71, 4422_P1_J3.71, 4423_P2_J1.102, 4425_TM_J1.68, 4429_FMT_J1.37
DPEBS08*: 4402_DPL_J2.9, 4408_P3_J1.102, 4422_P1_J3.104, 4423_P2_J2.5, 4425_TM_J1.69, 4429_FMT_J1.57
DPEBS09*: 4402_DPL_J2.10, 4408_P3_J1.104, 4422_P1_J3.106, 4423_P2_J2.6, 4425_TM_J1.70, 4429_FMT_J1.59
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
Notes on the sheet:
P2 (4K)
FLOATING MULTIPLIER
PDP-11 I/F
FLOATING ADDER
FMT
DATA PAD RIGHT
UNIBUS XFER
SPARE
MAIN DATA
P1 (4K)
DATA PAD LEFT
TABLE MEMORY

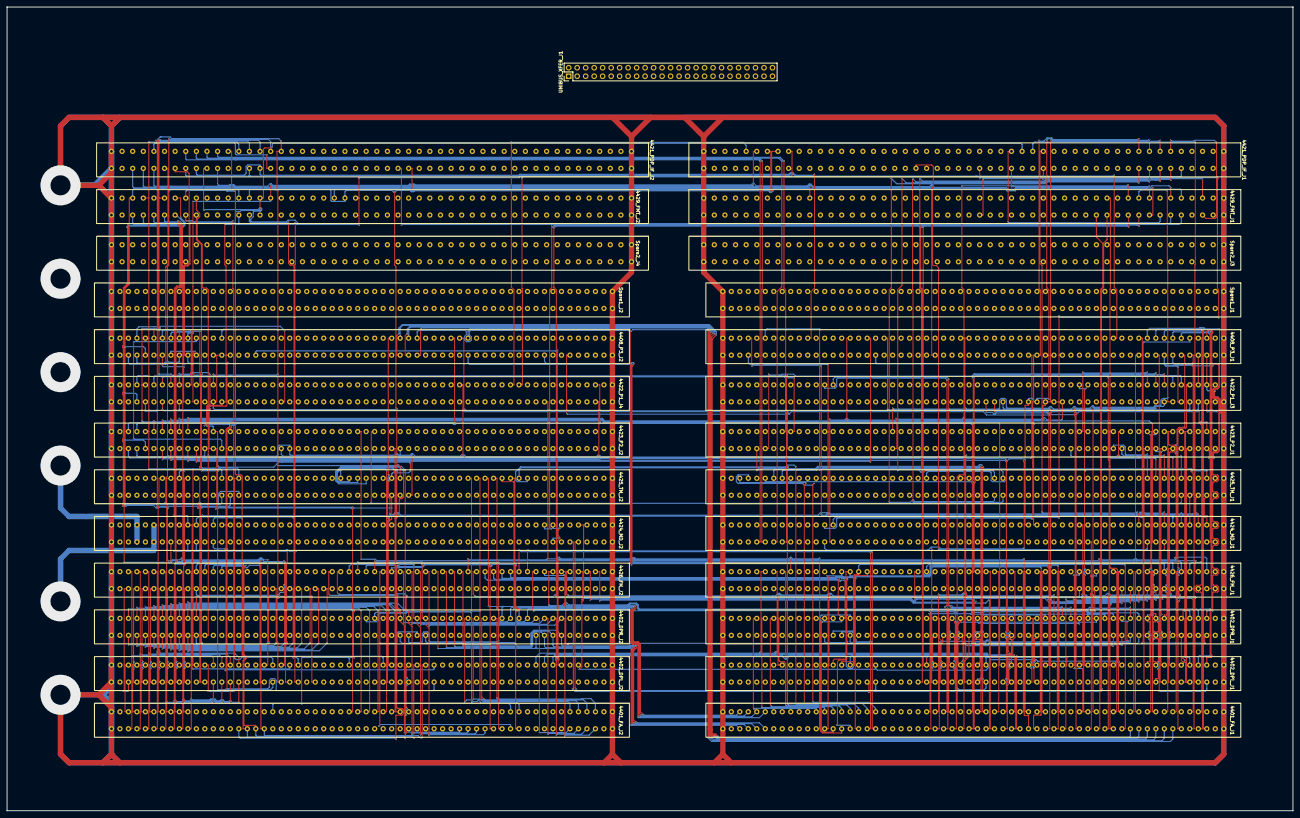
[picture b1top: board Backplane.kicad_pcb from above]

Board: 6 copper layers, 384.7 x 240.4 mm, 27 parts (0 on the bottom side), 757 nets.

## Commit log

2025-08-09 2025/8/8
2025-08-17 2025/8/17
2026-01-04 2026/1/4
2026-01-06 2026/1/6
2026-01-07 2026/1/7
2026-01-08 2026/1/8
2026-01-09 2026/1/9
